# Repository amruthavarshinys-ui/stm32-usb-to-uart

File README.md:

# STM32 USB to UART Converter (Work in Progress)

## Overview
This project is a USB to UART converter designed using an STM32 microcontroller.  
The goal is to enable communication between a computer (USB) and UART-based devices.

## Features
- STM32-based design
- USB communication interface
- UART output pins
- 3.3V power regulation
- Custom PCB designed using KiCad

## Tools Used
- KiCad (for schematic and PCB design)
- STM32 ecosystem

## Project Files
- Schematic (.kicad_sch)
- PCB Layout (.kicad_pcb)
- Project file (.kicad_pro)

## Current Status
  Work in Progress  
- PCB design completed  
- DRC errors present  
- Not yet fabricated or tested  

## Known Issues
- Unconnected vias
- Grounding issues
- Routing needs optimization

## What I Learned
- Designing a PCB from schematic
- Working with STM32 microcontrollers
- USB and UART interface basics
- Using KiCad for PCB design

## Next Steps
- Fix DRC errors
- Improve PCB layout
- Generate Gerber files
- Fabricate PCB
- Test hardware functionality

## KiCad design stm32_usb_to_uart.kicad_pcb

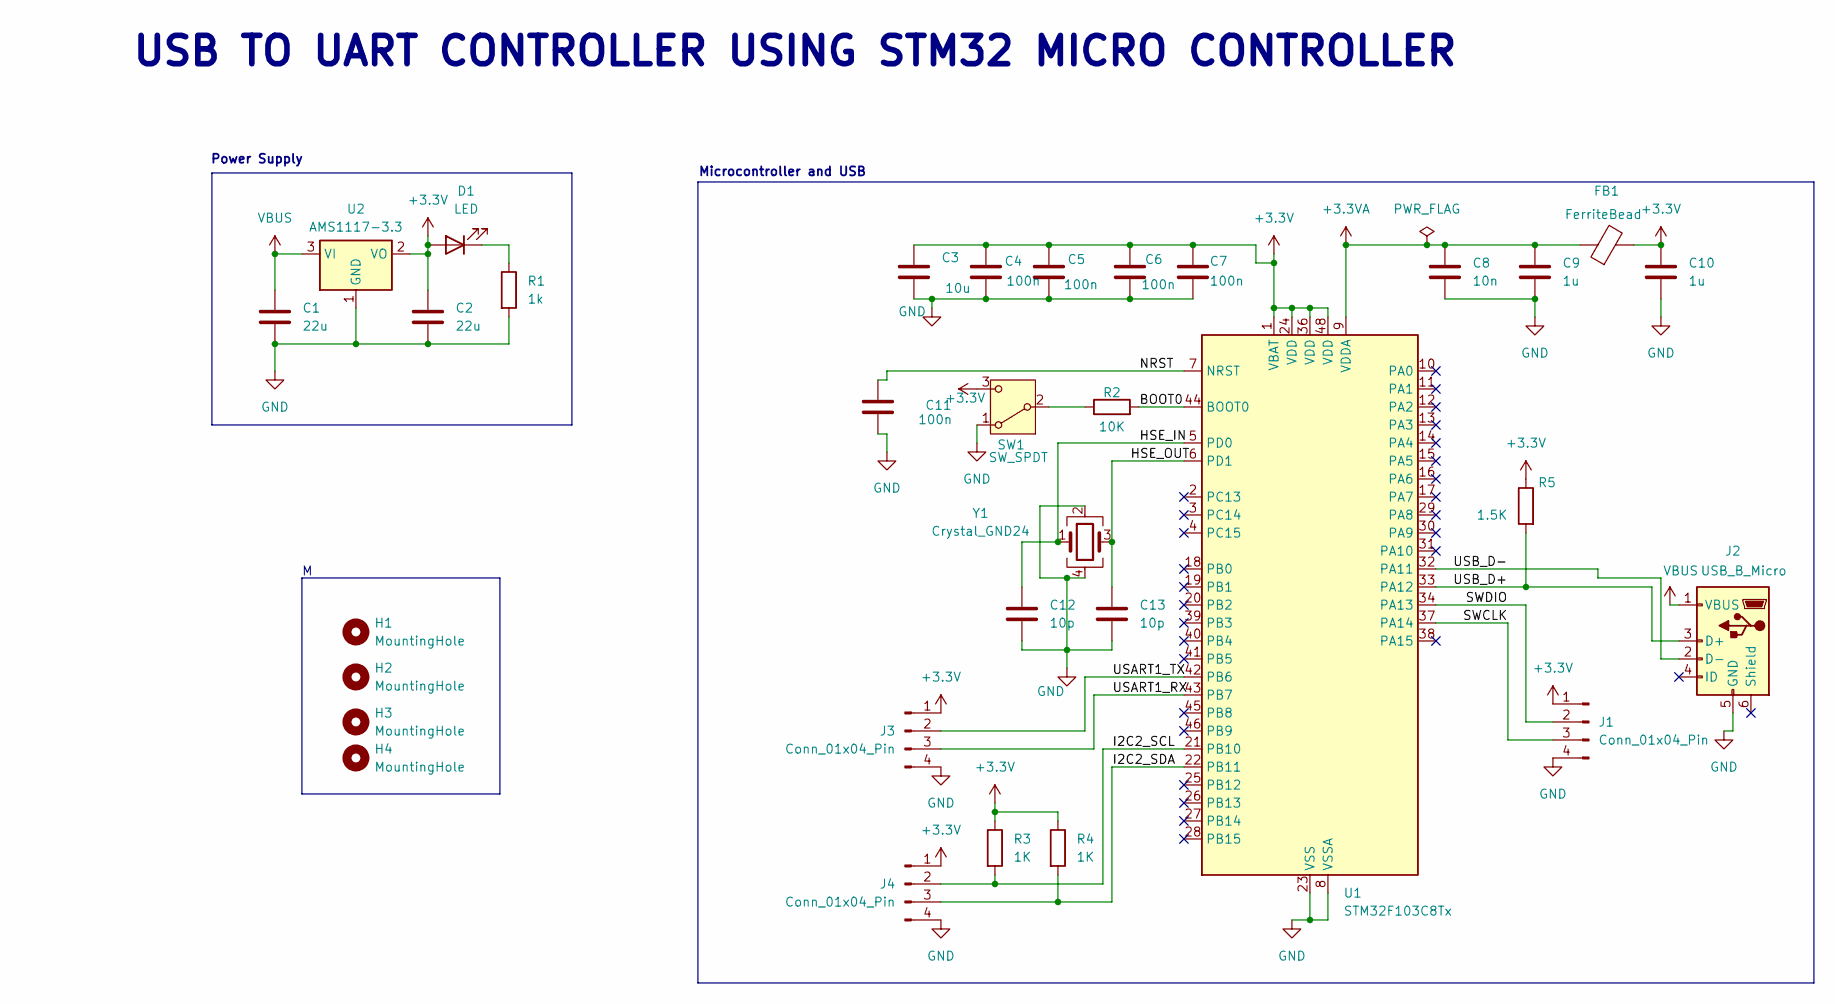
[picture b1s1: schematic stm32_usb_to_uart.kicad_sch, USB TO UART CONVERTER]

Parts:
C1, C2: 22u; C_0805_2012Metric
C3: 10u; C_0603_1608Metric
C4, C5, C6, C7, C11: 100n; C_0402_1005Metric
C8: 10n; C_0402_1005Metric
C9, C10: 1u; C_0402_1005Metric
C12, C13: 10p; C_0402_1005Metric
D1: LED; LED_0603_1608Metric
FB1: FerriteBead; L_0603_1608Metric
H1, H2, H3, H4: MountingHole; MountingHole_2.1mm
J1, J3, J4: Conn_01x04_Pin; PinHeader_1x04_P2.54mm_Vertical
J2: USB_B_Micro; USB_Micro-B_Wuerth_629105150521
R1: 1k; R_0402_1005Metric
R2: 10K; R_0402_1005Metric
R3, R4: 1K; R_0402_1005Metric
R5: 1.5K; R_0402_1005Metric
SW1: SW_SPDT; SW_SPDT_PCM12
U1: STM32F103C8Tx; LQFP-48_7x7mm_P0.5mm
U2: AMS1117-3.3; SOT-223-3_TabPin2
Y1: Crystal_GND24; Crystal_SMD_3225-4Pin_3.2x2.5mm

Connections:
+3.3V: C2.1, C3.1, C4.1, C5.1, C6.1, C7.1, C10.1, D1.2 (A), FB1.2, J1.1, J3.1, J4.1, R3.1, R4.1, R5.1, SW1.3 (C), U1.1 (VBAT), U1.24 (VDD), U1.36 (VDD), U1.48 (VDD), U2.2 (VO)
+3.3VA: C8.1, C9.1, FB1.1, U1.9 (VDDA)
/BOOT0: R2.2, U1.44 (BOOT0)
/HSE_IN: C12.1, U1.5 (PD0), Y1.1
/HSE_OUT: C13.1, U1.6 (PD1), Y1.3
/I2C2_SCL: J4.2, R3.2, U1.21 (PB10)
/I2C2_SDA: J4.3, R4.2, U1.22 (PB11)
/NRST: C11.1, U1.7 (NRST)
/SWCLK: J1.3, U1.37 (PA14)
/SWDIO: J1.2, U1.34 (PA13)
/USART1_RX: J3.3, U1.43 (PB7)
/USART1_TX: J3.2, U1.42 (PB6)
/USB_D+: J2.3 (D+), R5.2, U1.33 (PA12)
/USB_D-: J2.2 (D-), U1.32 (PA11)
GND: C1.2, C2.2, C3.2, C4.2, C5.2, C6.2, C7.2, C8.2, C9.2, C10.2, C11.2, C12.2, C13.2, J1.4, J2.5 (GND), J3.4, J4.4, R1.2, SW1.1 (A), U1.8 (VSSA), U1.23 (VSS), U1.35 (VSS), U1.47 (VSS), U2.1 (GND), Y1.2, Y1.4
unnamed: D1.1 (K), R1.1
unnamed: R2.1, SW1.2 (B)
VBUS: C1.1, J2.1 (VBUS), U2.3 (VI)

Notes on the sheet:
Microcontroller and USB
Power Supply
USB TO UART CONTROLLER USING STM32 MICRO CONTROLLER

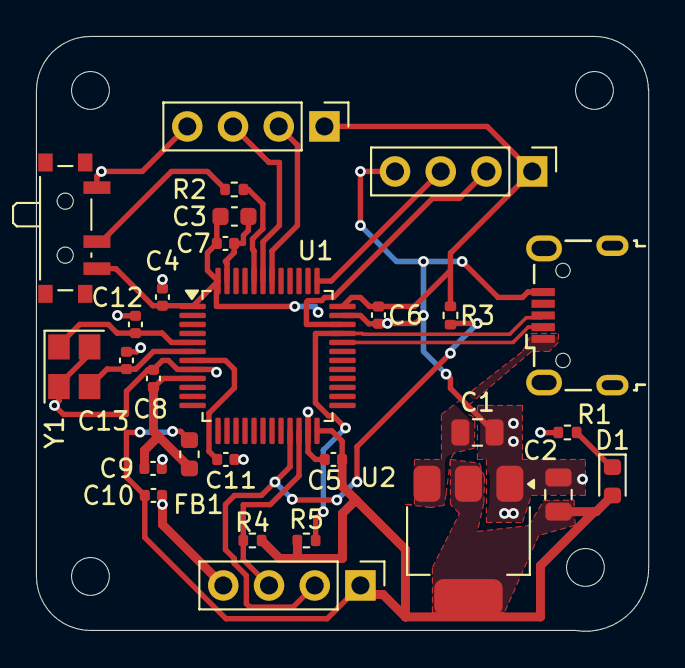
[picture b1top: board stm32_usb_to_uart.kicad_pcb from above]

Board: 2 copper layers, 34.0 x 33.0 mm, 32 parts (0 on the bottom side), 18 nets.

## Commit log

2026-03-24 Add files via upload
    Initial upload - STM32 USB to UART (WIP)
2026-03-24 Add files via upload
    Images
